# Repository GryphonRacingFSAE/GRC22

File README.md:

# GRC22
Repository for all firmware and related software on Gryphon Racing's 2022-2024 car.

## Quick Links
- Firmware
  - [Vehicle Control Unit (VCU)](https://github.com/GryphonRacingFSAE/GRC22/tree/main/VCU-Firmware)
  - [Remote Logging Module (RLM)](https://github.com/GryphonRacingFSAE/GRC22/tree/main/Remote-Logging-Module)
  - [Segment Monitoring Unit(s) (SMU)](https://github.com/GryphonRacingFSAE/GRC22/tree/main/SMU-Firmware)
  - [Dash](https://github.com/GryphonRacingFSAE/GRC22/tree/main/Dash)
- Collections
  - [KiCAD Component Library](https://github.com/GryphonRacingFSAE/GRC22/tree/main/KiCAD-Component-Library)
  - [DBC Files](https://github.com/GryphonRacingFSAE/GRC22/tree/main/DBCs)

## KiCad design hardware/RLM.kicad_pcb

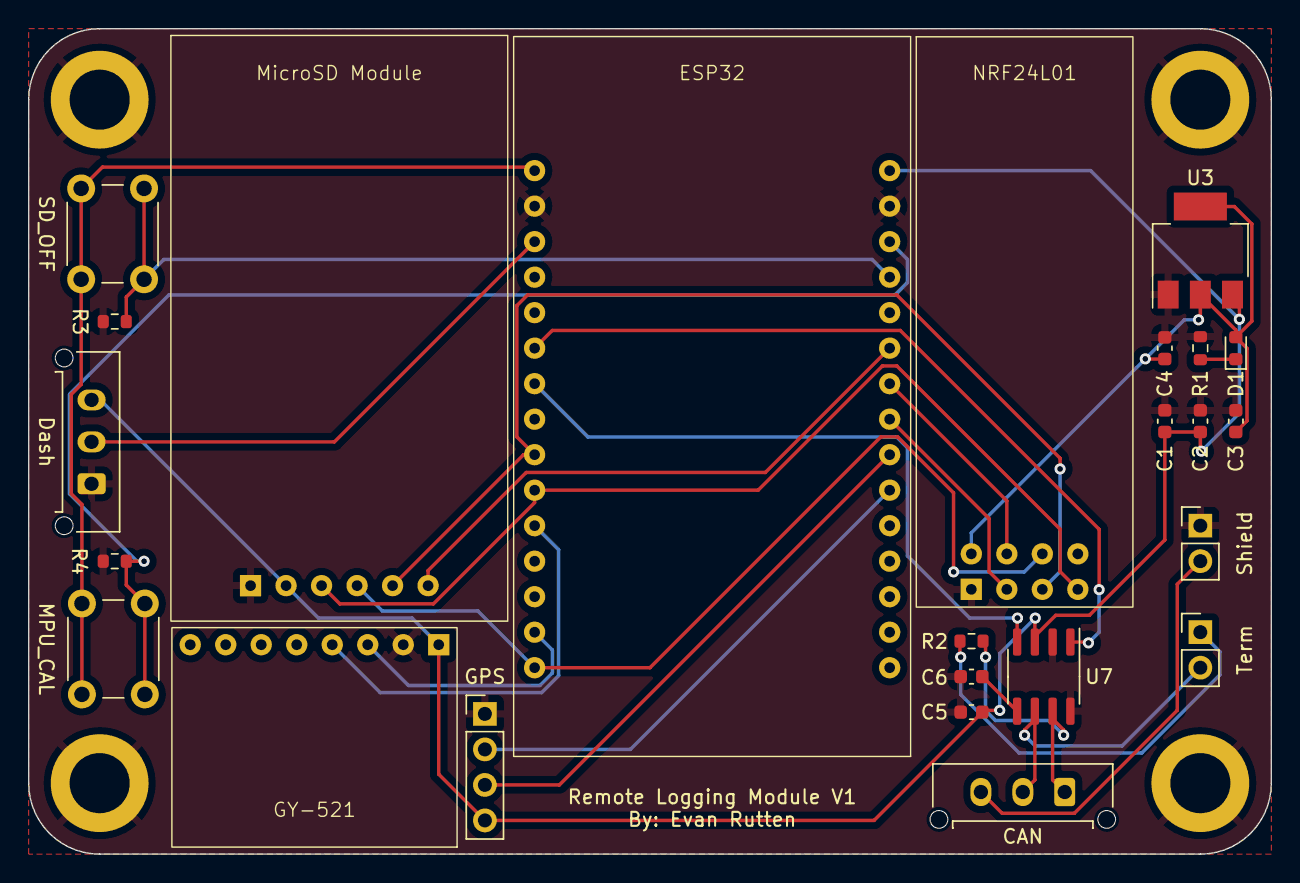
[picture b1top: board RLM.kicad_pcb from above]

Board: 2 copper layers, 88.9 x 59.1 mm, 28 parts (0 on the bottom side), 25 nets.

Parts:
C1, C3: 10u; C_0603_1608Metric
C2, C4: 1u; C_0603_1608Metric
C5, C6: 100nF; C_0603_1608Metric
CAN: Conn_01x03; Molex_Micro-Fit_3.0_43650-0315_1x03_P3.00mm_Vertical
D1: LED; LED_0603_1608Metric
Dash: Conn_01x03; Molex_Micro-Fit_3.0_43650-0315_1x03_P3.00mm_Vertical
ESP32: ESP32
GPS: BN-220; PinHeader_1x04_P2.54mm_Vertical
GY-521: GY-521
H1, H2, H3, H4: MountingHole; MountingHole_4.3mm_M4_ISO14580_Pad
MPU_CAL: SW_Push; SW_PUSH_6mm
MicroSD Module: MicroSD Module; MicroSD-Module
NRF24L01: NRF24L01
R1: 1k; R_0603_1608Metric
R2: 120; R_0603_1608Metric
R3, R4: 10k; R_0603_1608Metric
SD_OFF: SW_Push; SW_PUSH_6mm
Shield: Shielding; PinHeader_1x02_P2.54mm_Vertical
Term: Termination; PinHeader_1x02_P2.54mm_Vertical
U3: AP1117-33; SOT-223-3_TabPin2
U7: MCP2562-E-SN; SOIC-8_3.9x4.9mm_P1.27mm

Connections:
+3.3V: ESP32.16 (3V3), MPU_CAL.1, SD_OFF.1
+5V: C1.1, C2.1, C5.1, Dash.3, ESP32.15 (VIN), GPS.4 (VCC), GY-521.1 (VCC), MicroSD Module.2 (VCC), U3.3 (VI), U7.3 (VDD)
CAN_RX: ESP32.22 (TX2), U7.4 (RXD)
CAN_TX: ESP32.21 (RX2), U7.1 (TXD)
GLV+: C6.1, U7.5 (Vio)
GND: C1.2, C2.2, C3.2, C4.2, C5.2, C6.2, Dash.1, ESP32.14 (GND), ESP32.17 (GND), GPS.1 (GND), GY-521.2 (GND), H1.1, H2.1, H3.1, H4.1, MicroSD Module.1 (GND), NRF24L01.1 (GND), R1.2, R3.2, R4.2, Shield.1 (A), U3.1 (GND), U7.2 (VSS), U7.8 (STBY)
GPS_RX: ESP32.7 (D33), GPS.3 (RX)
GPS_TX: ESP32.6 (D32), GPS.2 (TX)
I2C_SCL: ESP32.29 (D22), GY-521.3 (SCL)
I2C_SDA: ESP32.26 (D21), GY-521.4 (SDA)
MPU_CAL: ESP32.13 (D13), MPU_CAL.2, R4.1
NRF_CE: ESP32.8 (D25), NRF24L01.3 (CE)
NRF_CSN: ESP32.9 (D26), NRF24L01.4 (CSN)
NRF_VCC: C3.1, C4.1, D1.2 (A), NRF24L01.2 (VCC), U3.2 (VO)
unnamed: D1.1 (K), R1.1
unnamed: CAN.1, R2.1, U7.7 (CANH)
unnamed: CAN.2, Term.2 (B), U7.6 (CANL)
unnamed: CAN.3, Shield.2 (B)
unnamed: R2.2, Term.1 (A)
SD_CS: ESP32.10 (D27), MicroSD Module.6 (CS)
SD_OFF: ESP32.12 (D12), R3.1, SD_OFF.2
SPI_MISO: ESP32.25 (D19), MicroSD Module.3 (MISO), NRF24L01.7 (MISO)
SPI_MOSI: ESP32.30 (D23), MicroSD Module.4 (MOSI), NRF24L01.6 (MOSI)
SPI_SCK: ESP32.24 (D18), MicroSD Module.5 (CLK), NRF24L01.5 (SCK)
V_SENSE: Dash.2, ESP32.18 (D15)

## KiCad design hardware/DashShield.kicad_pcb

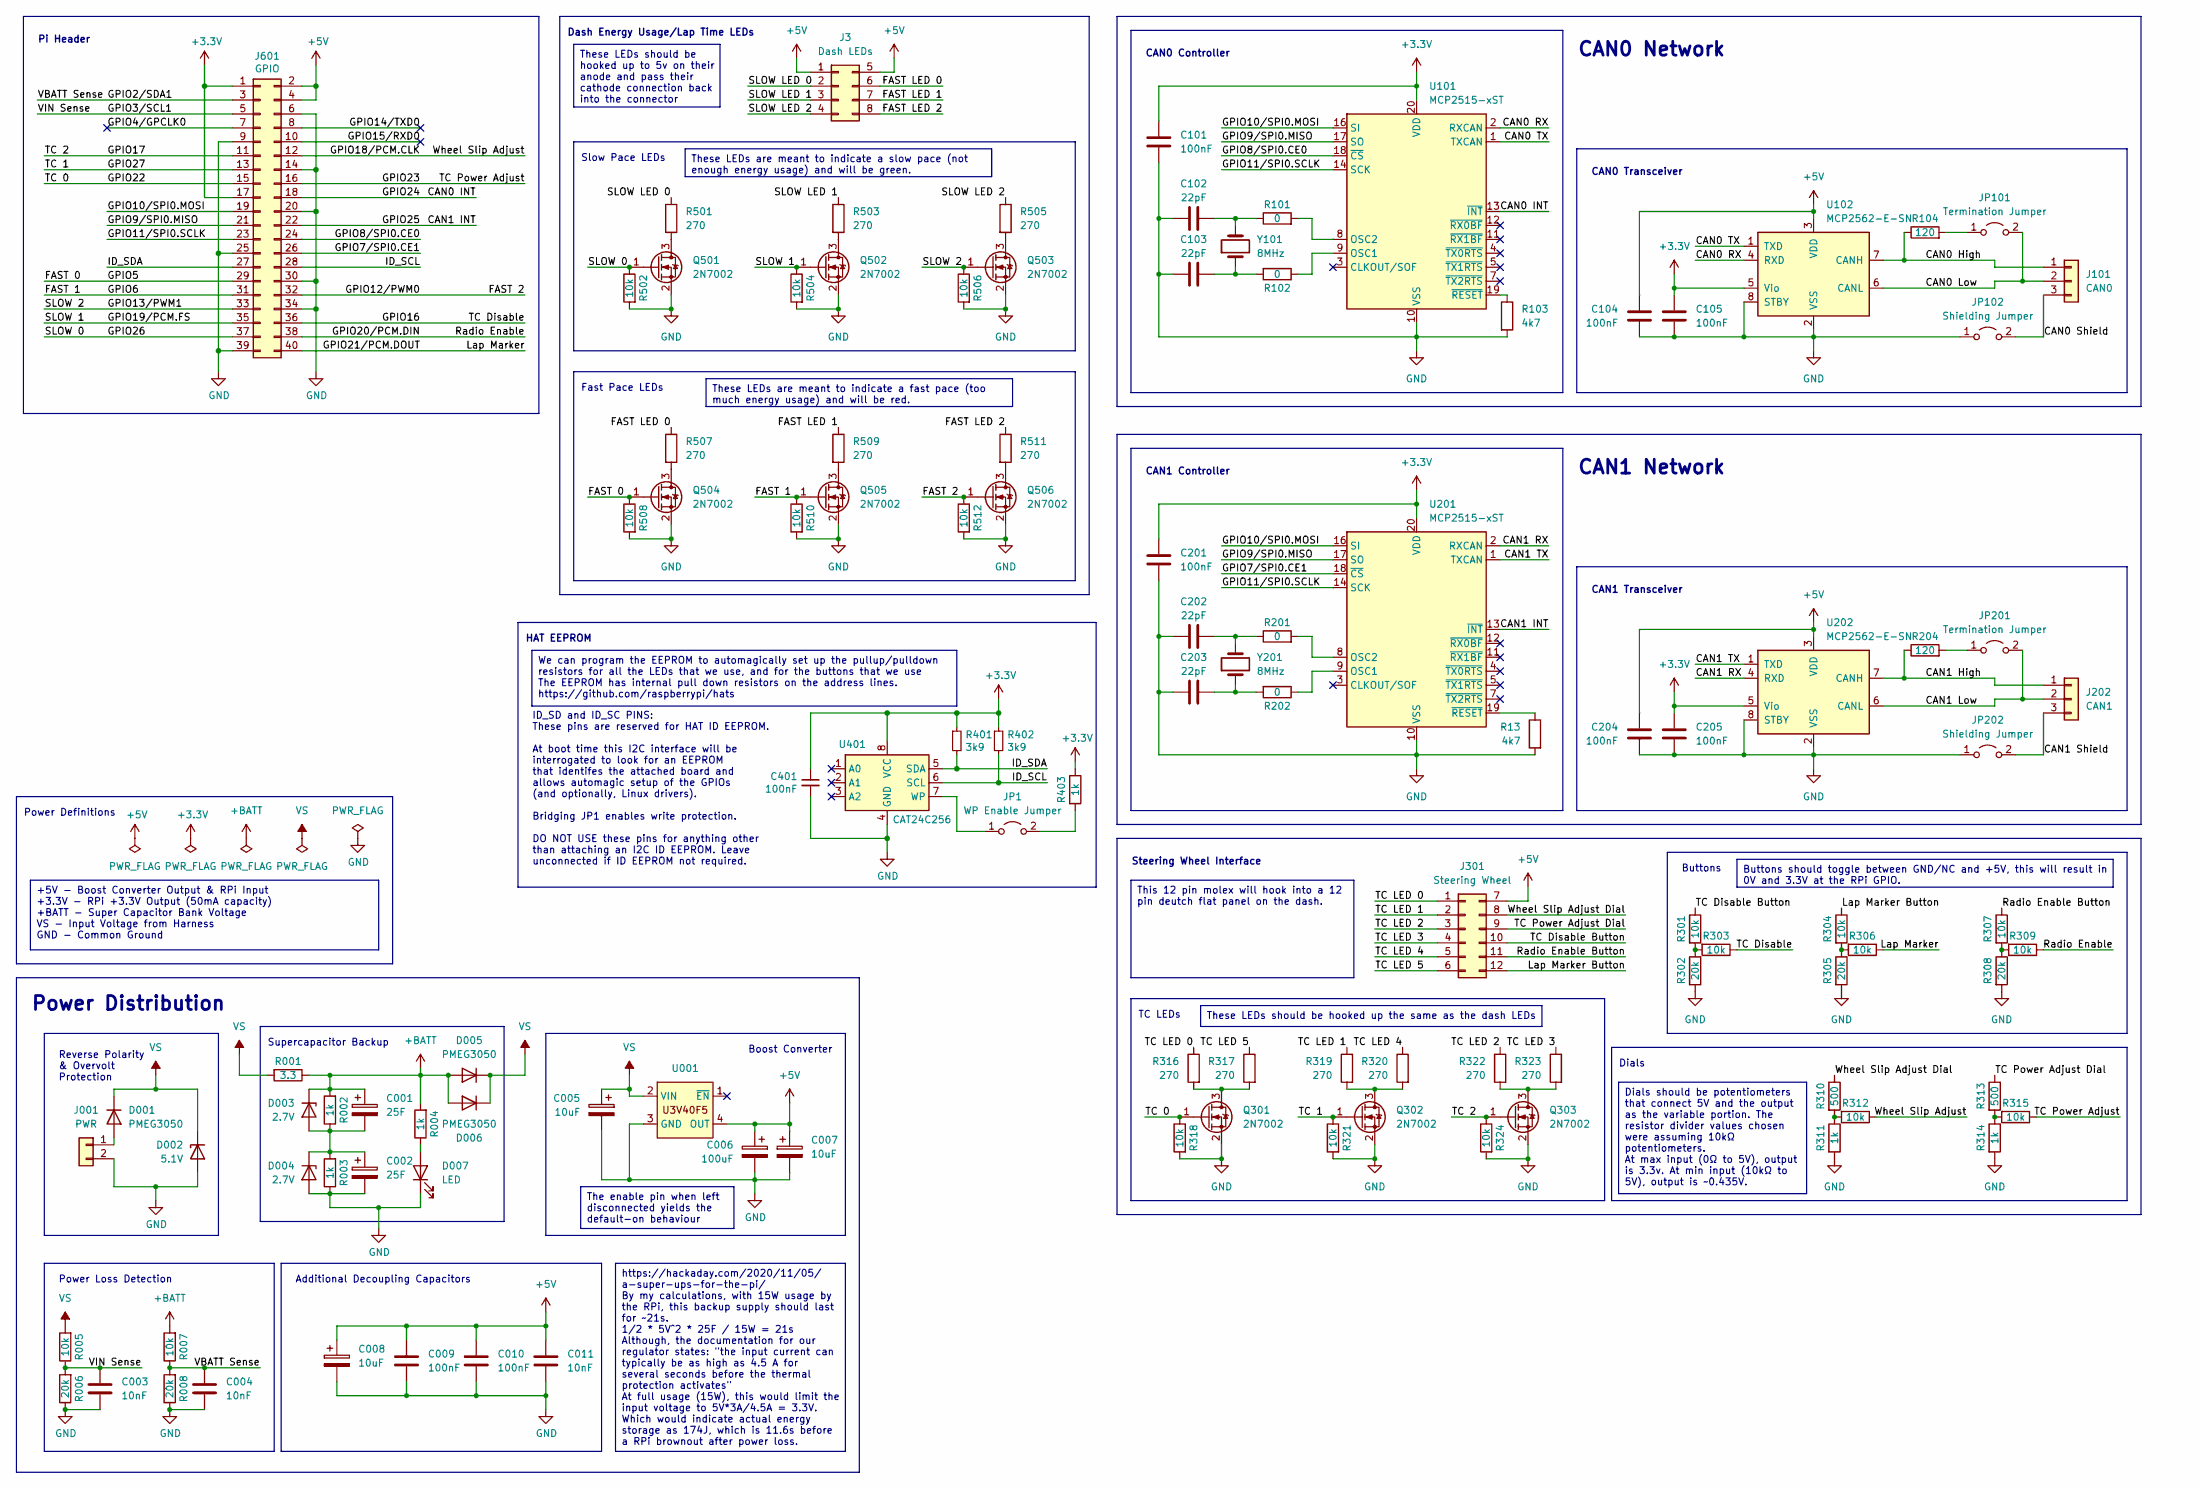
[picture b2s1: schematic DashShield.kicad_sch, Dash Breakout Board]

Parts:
C001, C002: 25F; CP_Radial_D16.0mm_P7.50mm
C003, C004, C011: 10nF; C_0603_1608Metric
C005, C007, C008: 10uF; CP_Radial_D5.0mm_P2.50mm
C006: 100uF; CP_Radial_D5.0mm_P2.50mm
C009, C010, C101, C104, C105, C201, C204, C205, C401: 100nF; C_0603_1608Metric
C102, C103, C202, C203: 22pF; C_0603_1608Metric
D001, D005, D006: PMEG3050; D_SOD-128
D002: 5.1V; D_SMA
D003, D004: 2.7V; SOT-23
D007: LED; LED_0603_1608Metric
J001: PWR; Molex_Micro-Fit_3.0_43650-0215_1x02_P3.00mm_Vertical
J3: Dash LEDs; Molex_Micro-Fit_3.0_43045-0812_2x04_P3.00mm_Vertical
J101: CAN0; Molex_Micro-Fit_3.0_43650-0315_1x03_P3.00mm_Vertical
J202: CAN1; Molex_Micro-Fit_3.0_43650-0315_1x03_P3.00mm_Vertical
J301: Steering Wheel; Molex_Micro-Fit_3.0_43045-1212_2x06_P3.00mm_Vertical
J601: GPIO; PinSocket_2x20_P2.54mm_Vertical
JP1: WP Enable Jumper; PinHeader_1x02_P2.54mm_Vertical
JP101, JP201: Termination Jumper; PinHeader_1x02_P2.54mm_Vertical
JP102, JP202: Shielding Jumper; PinHeader_1x02_P2.54mm_Vertical
Q301, Q302, Q303, Q501, Q502, Q503, Q504, Q505, Q506: 2N7002; SOT-23
R001: 3.3; R_0603_1608Metric
R002, R003, R004, R311, R314, R403: 1k; R_0603_1608Metric
R005, R007, R301, R303, R304, R306, R307, R309, R312, R315, R318, R321, R324, R502, R504, R506, R508, R510, R512: 10k; R_0603_1608Metric
R006, R008, R302, R305, R308: 20k; R_0603_1608Metric
R13, R103: 4k7; R_0603_1608Metric
R101, R102, R201, R202: 0; R_0603_1608Metric
R104, R204: 120; R_0603_1608Metric
R310, R313: 500; R_0603_1608Metric
R316, R317, R319, R320, R322, R323, R501, R503, R505, R507, R509, R511: 270; R_0603_1608Metric
R401, R402: 3k9; R_0603_1608Metric
U001: U3V40x
U101, U201: MCP2515-xST; TSSOP-20_4.4x6.5mm_P0.65mm
U102, U202: MCP2562-E-SN; SOIC-8_3.9x4.9mm_P1.27mm
U401: CAT24C256; SOIC-8_3.9x4.9mm_P1.27mm
Y101, Y201: 8MHz; Crystal_SMD_HC49-SD

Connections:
+3.3V: C101.1, C105.1, C201.1, C205.1, C401.1, J601.1, J601.17, R401.1, R402.1, R403.1, U101.20 (VDD), U102.5 (Vio), U201.20 (VDD), U202.5 (Vio), U401.8 (VCC)
+5V: C006.1, C007.1, C008.1, C009.1, C010.1, C011.1, C104.1, C204.1, J3.1, J3.5, J301.7, J601.2, J601.4, U001.4 (OUT), U102.3 (VDD), U202.3 (VDD)
+BATT: C001.1, D003.3 (K), D005.2 (A), D006.2 (A), R001.1, R002.2, R004.2, R007.2
/CAN0 High: J101.1, R104.1, U102.7 (CANH)
/CAN0 INT: J601.18, U101.13 (~INT)
/CAN0 Low: J101.2, JP101.2 (B), U102.6 (CANL)
/CAN0 RX: U101.2 (RXCAN), U102.4 (RXD)
/CAN0 Shield: J101.3, JP102.2 (B)
/CAN0 TX: U101.1 (TXCAN), U102.1 (TXD)
/CAN1 High: J202.1, R204.1, U202.7 (CANH)
/CAN1 INT: J601.22, U201.13 (~INT)
/CAN1 Low: J202.2, JP201.2 (B), U202.6 (CANL)
/CAN1 RX: U201.2 (RXCAN), U202.4 (RXD)
/CAN1 Shield: J202.3, JP202.2 (B)
/CAN1 TX: U201.1 (TXCAN), U202.1 (TXD)
/FAST 0: J601.29, Q504.1 (G), R508.1
/FAST 1: J601.31, Q505.1 (G), R510.1
/FAST 2: J601.32, Q506.1 (G), R512.1
/FAST LED 0: J3.6, R507.1
/FAST LED 1: J3.7, R509.1
/FAST LED 2: J3.8, R511.1
/GPIO2/SDA1: C004.1, J601.3, R007.1, R008.2
/GPIO3/SCL1: C003.1, J601.5, R005.1, R006.2
/GPIO4/GPCLK0: J601.7
/GPIO7/SPI0.CE1: J601.26, U201.18 (~CS)
/GPIO8/SPI0.CE0: J601.24, U101.18 (~CS)
/GPIO9/SPI0.MISO: J601.21, U101.17 (SO), U201.17 (SO)
/GPIO10/SPI0.MOSI: J601.19, U101.16 (SI), U201.16 (SI)
/GPIO11/SPI0.SCLK: J601.23, U101.14 (SCK), U201.14 (SCK)
/GPIO13/PWM1: J601.33, Q503.1 (G), R506.1
/GPIO14/TXD0: J601.8
/GPIO15/RXD0: J601.10
/GPIO16: J601.36, R303.1
/GPIO17: J601.11, Q303.1 (G), R324.1
/GPIO18/PCM.CLK: J601.12, R312.1
/GPIO19/PCM.FS: J601.35, Q502.1 (G), R504.1
/GPIO20/PCM.DIN: J601.38, R309.1
/GPIO21/PCM.DOUT: J601.40, R306.1
/GPIO22: J601.15, Q301.1 (G), R318.1
/GPIO23: J601.16, R315.1
/GPIO26: J601.37, Q501.1 (G), R502.1
/GPIO27: J601.13, Q302.1 (G), R321.1
/ID_SCL: J601.28, R402.2, U401.6 (SCL)
/ID_SDA: J601.27, R401.2, U401.5 (SDA)
/Lap Marker Button: J301.12, R304.1
/Radio Enable Button: J301.11, R307.1
/SLOW LED 0: J3.2, R501.1
/SLOW LED 1: J3.3, R503.1
/SLOW LED 2: J3.4, R505.1
/TC Disable Button: J301.10, R301.1
/TC LED 0: J301.1, R316.1
/TC LED 1: J301.2, R319.1
/TC LED 2: J301.3, R322.1
/TC LED 3: J301.4, R323.1
/TC LED 4: J301.5, R320.1
/TC LED 5: J301.6, R317.1
/TC Power Adjust Dial: J301.9, R313.1
/Wheel Slip Adjust Dial: J301.8, R310.1
GND: C002.2, C003.2, C004.2, C005.2, C006.2, C007.2, C008.2, C009.2, C010.2, C011.2, C101.2, C102.2, C103.1, C104.2, C105.2, C201.2, C202.2, C203.1, C204.2, C205.2, C401.2, D002.2 (A), D004.1 (A), D007.1 (K), J001.2, J601.6, J601.9, J601.14, J601.20, J601.25, J601.30, J601.34, J601.39, JP102.1 (A), JP202.1 (A), Q301.2 (S), Q302.2 (S), Q303.2 (S), Q501.2 (S), Q502.2 (S), Q503.2 (S), Q504.2 (S), Q505.2 (S), Q506.2 (S), R003.1, R006.1, R008.1, R13.2, R103.2, R302.2, R305.2, R308.2, R311.2, R314.2, R318.2, R321.2, R324.2, R502.2, R504.2, R506.2, R508.2, R510.2, R512.2, U001.3 (GND), U101.10 (VSS), U102.2 (VSS), U102.8 (STBY), U201.10 (VSS), U202.2 (VSS), U202.8 (STBY), U401.4 (GND)
unnamed: C102.1, R101.1, Y101.2
unnamed: C103.2, R102.2, Y101.1
unnamed: C202.1, R201.1, Y201.2
unnamed: C203.2, R202.2, Y201.1
unnamed: D001.2 (A), J001.1
unnamed: C001.2, C002.1, D003.1 (A), D004.3 (K), R002.1, R003.2
unnamed: D007.2 (A), R004.1
unnamed: JP1.1 (A), U401.7 (WP)
unnamed: JP1.2 (B), R403.2
unnamed: JP101.1 (A), R104.2
unnamed: JP201.1 (A), R204.2
unnamed: Q301.3 (D), R316.2, R317.2
unnamed: Q302.3 (D), R319.2, R320.2
unnamed: Q303.3 (D), R322.2, R323.2
unnamed: Q501.3 (D), R501.2
unnamed: Q502.3 (D), R503.2
unnamed: Q503.3 (D), R505.2
unnamed: Q504.3 (D), R507.2
unnamed: Q505.3 (D), R509.2
unnamed: Q506.3 (D), R511.2
unnamed: R301.2, R302.1, R303.2
unnamed: R304.2, R305.1, R306.2
unnamed: R307.2, R308.1, R309.2
unnamed: R310.2, R311.1, R312.2
unnamed: R313.2, R314.1, R315.2
unnamed: R102.1, U101.9 (OSC1)
unnamed: R101.2, U101.8 (OSC2)
unnamed: R103.1, U101.19 (~RESET)
unnamed: R202.1, U201.9 (OSC1)
unnamed: R201.2, U201.8 (OSC2)
unnamed: R13.1, U201.19 (~RESET)
VS: C005.1, D001.1 (K), D002.1 (K), D005.1 (K), D006.1 (K), R001.2, R005.2, U001.2 (VIN)

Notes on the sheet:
https://hackaday.com/2020/11/05/ a-super-ups-for-the-pi/ By my calculations, with 15W usage by the RPi, this backup supply should last for ~21s. 1/2 * 5V^2 * 25F / 15W = 21s Although, the documentation for our regulator states: "the input current can typically be as high as 4.5 A for several second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
These LEDs should be hooked up to 5v on their anode and pass their cathode connection back into the connector
Buttons should toggle between GND/NC and +5V, this will result in 0V and 3.3V at the RPi GPIO.
We can program the EEPROM to automagically set up the pullup/pulldown resistors for all the LEDs that we use, and for the buttons that we use The EEPROM has internal pull down resistors on the address lines. https://github.com/raspberrypi/hats
The enable pin when left disconnected yields the default-on behaviour
These LEDs are meant to indicate a slow pace (not enough energy usage) and will be green.
Dials should be potentiometers that connect 5V and the output as the variable portion. The resistor divider values chosen were assuming 10kΩ potentiometers. At max input (0Ω to 5V), output is 3.3v. At min input (10kΩ to 5V), output is ~0.435V.
This 12 pin molex will hook into a 12 pin deutch flat panel on the dash.
+5V - Boost Converter Output & RPi Input +3.3V - RPi +3.3V Output (50mA capacity) +BATT - Super Capacitor Bank Voltage VS - Input Voltage from Harness GND - Common Ground
These LEDs should be hooked up the same as the dash LEDs
These LEDs are meant to indicate a fast pace (too much energy usage) and will be red.
Power Loss Detection
Power Definitions
CAN1 Controller
Reverse Polarity & Overvolt Protection
Dials
ID_SD and ID_SC PINS: These pins are reserved for HAT ID EEPROM. At boot time this I2C interface will be interrogated to look for an EEPROM that identifes the attached board and allows automagic setup of the GPIOs (and optionally, Linux drivers). Bridging JP1 enables write protection. DO NOT USE th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
Buttons
Power Distribution
Fast Pace LEDs
TC LEDs
CAN1 Transceiver
Supercapacitor Backup
Steering Wheel Interface
CAN1 Network
Dash Energy Usage/Lap Time LEDs
HAT EEPROM
Slow Pace LEDs
CAN0 Network
Pi Header
CAN0 Transceiver
CAN0 Controller
Additional Decoupling Capacitors
Boost Converter

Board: 2 copper layers, 112 parts (0 on the bottom side), 88 nets, no tracks yet.

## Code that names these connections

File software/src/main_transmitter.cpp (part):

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//==============================================================================

// GPIO
#define SD_OFF GPIO_NUM_12
#define MPU_CAL GPIO_NUM_13
#define V_SENSE GPIO_NUM_15
#define CAN_TX GPIO_NUM_16
#define CAN_RX GPIO_NUM_17
#define NRF_CE GPIO_NUM_25
#define NRF_CSN GPIO_NUM_26
#define SD_CS GPIO_NUM_27
#define GPS_TX GPIO_NUM_32
#define GPS_RX GPIO_NUM_33

static uint16_t global_can_message_count = 0;
static uint32_t global_can_bit_count = 0;
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
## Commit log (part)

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2023-09-25 fix: add custom proto to receiver code
2023-09-25 feat: add MPU6050 proto
2023-09-27 fix: swap GPS serial line
2023-09-27 feat: multiple proto message detection (WIP)
2023-10-03 fix: swap out accel/gyro library
2023-10-03 chore: clean up project folder
2023-10-04 feat: add debug messages on transmitter end
2023-10-05 feat: thermistor recalculations
    BREAKING CHANGE: Encountered bug where variable declaration is functioning sporadically, leading to values to be 0 or not exist
    Revert "feat: thermistor recalculations"
    This reverts commit ce3d29adfbcb9b2d0b7a816933b9076c2f4b341b.
    Revert "Revert "feat: thermistor recalculations""
    This reverts commit becb8420c5892b38bf33213f98f2ed2346578c9f.
2023-10-05 chore: add KiCad project files
2023-10-05 Add external modules
2023-10-06 refactor: scanning single select line on MUX
2023-10-06 chore: separate software + hardware
2023-10-06 chore: rename folders to match other repos
2023-10-06 feat: add team KiCad library
2023-10-06 chore: swap to personal branch on submodule
2023-10-06 feat: add nRF module
2023-10-07 feat: add CAN controller & transceivers
2023-10-07 chore: add CI
2023-10-07 chore: fix CI to work with new file structure
2023-10-08 feat: add MPU-6050
2023-10-08 feat: initial CAN interfaces
2023-10-08 feat: add U3V40x libraries
2023-10-08 feat: finish power supply
2023-10-09 feat: add GPS and SD components
2023-10-09 fix: u3v40 footprint and symbol pin assignment issues
2023-10-09 feat: add NRF adapter schematic
2023-10-10 feat: add NRF adapter layout
2023-10-10 feat: update NRF module
2023-10-10 chore: submodule changes
2023-10-10 fix: apply Ayden's design review
2023-10-12 feat: add ESP32, NRF, GY footprints
2023-10-12 feat: add GY-521 footprint
2023-10-13 refactor: changed function name
2023-10-13 refactor: comments added
2023-10-16 chore: reorganize schematic
2023-10-18 feat: complete SD card file output
2023-10-18 style: fix formatting
2023-10-19 feat: add ESP32 power input
2023-10-23 feat: implement simple mpu offset
2023-10-24 feat: add mpu calibration
2023-10-26 chore: update ESP32 pin locations
2023-10-26 feat: add pushbuttons
2023-10-26 fix: add missing pad to GY-521 footprint
2023-10-26 feat: initial layout
2023-10-27 feat: layout v2
2023-10-31 feat: move all ports to the same side
2023-10-31 feat: update symbols to have VCC up and GND down
2023-11-08 Dallas Change to Dash
    Dallas made a bunch of changes to dash
2023-11-08 auto generate: code auto-generation from ioc
2023-11-16 fix: build issues
2023-11-17 refactor: replace all indents with tabs
2023-11-18 fix: CAN resistances, ground pour, logo
2023-11-19 feat: add gerbers
2023-11-20 chore: remove gerbers
2023-11-22 refactor: Comments added
    - Added function definitions for startThermistorMonitorTask() and adcChangeChannel()
    - Added comment in the ThermistorMonitor.h file for how thermistor data is stored and formatted
2023-12-17 added tc tuning qml
2023-12-21 font changed to consolas
2023-12-25 feat: change to 16 channel MUX and added DIP switch
2023-12-25 fix: reverted back to 5 pin JTAG connectivity
2023-12-25 fix: made the module id easier to access
2023-12-28 tc screen w/frontend (fake) VCU
2023-12-28 removed unnecessary import
2024-01-04 feat: finished VCU dbc
2024-01-08 feat: MVP for single module TEM configurations
2024-01-08 ci: add autobuild/compile checking
2024-01-09 fix: multiple modules connecting to BMS
2024-01-09 refactor: added constants for pins, changed pins for sd and gps
2024-01-09 ci: fix formatting workflows
2024-01-09 style: clang & cmake format
2024-01-09 ci: set working directory
2024-01-09 feat: thermistor temps screen
2024-01-10 feat: first revision of new interface method
2024-01-10 ci: change working directory for jobs
2024-01-10 fix: missing signal
2024-01-10 fix: variable naming & missing member variable
2024-01-10 ci: don't try to login to the conan server
2024-01-10 fix: missing tc tune variables
2024-01-10 removed unused constants
2024-01-10 fix: performance issue and build failures
2024-01-10 fix: change to .find
2024-01-10 style: clang-format
2024-01-11 fix: error with filtering and DBC dispatching
2024-01-11 chore: add back V_SENSE pin
2024-01-15 feat: add CAN functionality
2024-01-17 fix: apply MPU calibration within read function
2024-01-18 chore: finished refactor
2024-01-18 fix: console formatting
2024-01-18 fix: make format check work
2024-01-18 fix: adjust timings
2024-01-19 chore: move files into submodule
2024-01-22 chore: update BMS DBC
2024-01-25 fix: add missing flag
2024-01-27 feat: added cell voltages screen
2024-01-29 fix: display correct decimals
2024-01-29 fix: bms can filter
2024-01-31 fix: adjust for physical configuration of BMS
2024-01-31 feat: convert MPU data to correct units
2024-02-01 fix: fixed display precision
2024-02-01 chore: upload new DBC for BMS
2024-02-01 fix: proper precision
2024-02-01 fix: readme
2024-02-02 feat: added parameters to tc tuning
2024-02-06 chore: update dash and VCU DBC files
2024-02-07 chore: add additional informational values for VCU state
2024-02-16 Timing configurations set
    Board is accurately reading rising edges of frequency
    Frequency is set to zero at approx 3Hz (equates to 0.5 km/h)
    Need to start converting Hz to Rpm and then start populating wheelspeed array and adding same formula for all 4 sensors
    Possible look into different period for increased accuracy at higher speeds for future use of TC
2024-02-17 Updated ReadME file
    ReadMe has a new section for algorithms used (contains the derivation for the period calculation for wheel speed sensor timing)
2024-02-17 fix: compile issues
2024-02-22 fix: message lengths
2024-02-24 chore: add SMU DBC
2024-02-24 chore: rename SMU dbc
2024-02-24 feat: add dbc to protobuf script
2024-02-24 chore: remove SD card code
2024-02-24 "fix": dbcs
2024-02-24 chore: clean up .ini file
2024-02-24 fix: make DBC conversion work
2024-02-26 fix: rename duplicate message name
2024-02-26 feat: working mcap saving with arbitrary CAN data
2024-02-27 feat: add websocket support to busdump
2024-02-29 fix: formatting & small bugs
2024-02-29 fix: alter importing of python dbc -> proto script
2024-02-29 ci: missed cloning submodules
2024-02-29 ci: install cantools alongside conan
2024-02-29 ci: use latest conan 1 version
2024-02-29 ci: force root for docker?
2024-02-29 ci: remove extraneous -o option
2024-02-29 ci: remove sudo from conan command
2024-02-29 refactor: big adjustments, isolate Foxglove logger
2024-02-29 fix: linking issues
2024-02-29 feat: add file saving folder structure
2024-03-03 chore: progress update for restransmitting server
2024-03-04 feat: convert can to twai
2024-03-05 fix: fixed issue with build_protos.py
2024-03-06 Wheelspeed Sensor update Ver 1.0
    comments added for all wheelspeed related variables and functions
    updated to use timer 3 channels (one per sensor)
    rpm calculation function created (utilizing formula mentioned within the readME file)
    will need further changes mainly for optimization and possible extra arrays (will be added post test on Wednesday)
    timer 3 channel gpio input pins need to be updated in correspondence with the wheelspeed sensor connections (currently connected to random pins)
2024-03-06 feat: working transmitting from ESP32 to foxglove
2024-03-06 4 sensors version 0.1
    Bugs are within program, pretty sure on what needs to be fixed, updated and fixed version should be uploaded on Thursday
2024-03-07 testing with 4 sensors
    i am sad
2024-03-09 fix: CAN message printing
2024-03-09 feat: merge RLM branches
2024-03-09 feat: wireless CAN
2024-03-10 docs: add DBC to CPP process
2024-03-10 docs: organize receiver code
2024-03-10 fix: use scons for build_protos.py
2024-03-10 fix: add CAN_2.proto to .gitignore
2024-03-14 Wheel speed function optimized
    No clue if it works needs to be tested.
2024-03-14 chore: update DBC for CM200
2024-03-14 requests resolved
    Still need to test functionality.
2024-03-15 All resolved **
2024-03-15 refactor: nuke transaction handler
2024-03-15 chore: remove python script
2024-03-15 feat: move all python to /scripts folder
2024-03-15 docs: update dbc to cpp output folder
2024-03-16 chore: update VCU dbc
2024-03-16 fix: RLM time and trajectory
2024-03-16 feat: add remaining CAN messages
2024-03-18 fix: script compilation issues
2024-03-18 fix: change MPU values to float
2024-03-18 docs: update DBC to CPP command
2024-03-18 fix: add back cantools generated files
2024-03-19 Fully functioning wheel speed
    Tested with all pins and readings are accurate up to max frequency. Deviation of 2hz (teeth/s) which results in being off by 4 rpm at max teeth freq of (960). At lower teeth/s the reading are pretty 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
2024-03-20 fix: move DBC file path on decode script
2024-03-21 pwm fixed
    fix: pwm is outputting proper frequencies
2024-03-21 feat: eliminated all mutexes and simplified logic across files
2024-03-22 resolved review requests
    Resolved requests in review
    Modified ReadME file to display all equations used
2024-03-27 feat: Pressure sensors
    needs to be tested
    needs checks for shorts
2024-04-01 working on print issue
2024-04-03 fix: pressure sensor logic
2024-04-04 fix: mux numbering
2024-04-08 feat: switch to json on the websocket server
2024-04-08 docs: add instructions for foxglove server
2024-04-09 feat: changes for sensors and verification
2024-04-12 feat: RTD, CAN messages, etc.
2024-04-17 fix: temporary change to torque map
    Typo fixes to the read me
2024-04-17 ci: update stm32cubeide version for ci
2024-04-21 chore: create separate foxglove folder
2024-04-22 chore: update dbcs
2024-04-22 fix: remove radio init serial message
2024-04-23 feat: various items fixed in regards to motor control.
2024-04-23 fix: add new library to requirements.txt
2024-04-24 fix: divide by zero issues
2024-04-24 chore: update dbcs for orion and vcu
2024-04-25 nuke
2024-04-28 feat: new VCU
2024-04-30 fix: length issue with vcu signal
2024-05-07 feat: add AMS fault control
2024-05-09 chore: remove RLM time
2024-05-10 feat: filter open circuit thermistors
2024-05-10 fix: update open circuit cell cutoff
2024-05-14 fix: pump speed & bms dtc decoding
2024-05-15 refactor: split all tasks into separate files
2024-05-16 feat: imd reading
    no CAN
2024-05-16 ci: add build checking
2024-05-16 style: format cpp
2024-05-16 fix: import file issue
2024-05-17 Feat: Finished IMD Resistance Decode
    Added can fixed resistance output
2024-05-17 Chore: Updated Documentation
2024-05-17 chore: add pump speed to VCU programming
2024-05-17 Feat: AMS chatter protection
2024-05-17 docs: fix formatting issue
2024-05-18 fix: lower CAN receive task delay
2024-05-18 fix: return on serial read function
2024-05-22 feat: large changes for onboard logging
2024-05-23 fix: imd, ams, pump
    imd issues fixed need to be replicated on can reciever
    ams issue fixed
    pump updated with new logic for better temp consistency
2024-05-26 fix: incorrect thermistor beta and temperature at ambient
2024-05-26 feat: transmit stored torque vals
2024-06-03 fix: syntax error
2024-06-03 feat: flow sensor
2024-06-04 style: cpp format
2024-06-04 incomplete: add filtered thermistors can message
2024-06-05 feat: pump idle speed & flow sensor rate
2024-06-05 Update SMU and VCU DBCs
2024-06-05 fix: failed thermistor isolation
2024-06-06 fix: divide by zero crash
2024-06-07 style: clang format
2024-06-08 Fix flow rate address
2024-06-10 feat: alter system health message
2024-06-10 feat add DTC mask messages
2024-06-10 feat: ams dtc mask can params
2024-06-11 fix: random bugs
2024-06-12 feat: add item into system health
2024-07-03 refactor: wheel speed sensors
    updated for 2 sensors in the front
2024-07-07 feat: adjustments for getting the motor spinning
2024-07-11 refactor: pump
    pump idle speed back to being controlled through EEPROM, updated default at 25%
2024-07-15 Merged Dash into subfolder
2024-07-15 Merged DBCs into subfolder
2024-07-15 Merged Remote-Logging-Module into subfolder
2024-07-15 Merged SMU-Firmware into subfolder
2024-07-15 Remove duplicate files
2024-07-15 Merged VCU-Firmware dallas/michigan into subfolder
2024-07-16 feat: rad fan
    rad fan always on (code is not tested may be subject to change)
2024-07-20 Start logging locally (WIP)
2024-07-21 Revert "Enable logging for Foxglove on external machines"
2024-07-21 Revert "Revert "Enable logging for Foxglove on external machines""
